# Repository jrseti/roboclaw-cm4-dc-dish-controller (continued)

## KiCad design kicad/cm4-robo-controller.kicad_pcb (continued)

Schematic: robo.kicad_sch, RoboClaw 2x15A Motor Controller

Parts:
A1: ROBOCLAW-2X15A-OEM; MOD-TH_ROBOCLAW-OEM-2X15A; MPN RoboClaw 2x15A OEM; LCSC Part N/A; not fitted
C57, C58, C59, C60, C61, C87, C88: 10nF; CAPC1005X55N; Voltage Rating 50V; Tolerance ±10%; MPN 0402B103K500CT; LCSC Part C301927
C62, C63, C83, C86: 100nF; CAPC1005X55N; Tolerance ±10%; Voltage Rating 16V; MPN CL05B104KO5NNNC; LCSC Part C1525
C80: 1uF; CAPC1608X95N; Tolerance ±10%; Voltage Rating 25V; MPN CL10A105KA8NNNC; LCSC Part C5673
C81, C89: 10uF; CAPC1608X95N; Tolerance ±20%; Voltage Rating 25V; MPN CL10A106MA8NRNC; LCSC Part C96446
D16, D18, D22, D27: TPESD0402G12V; DIOC1005X55N; MPN TPESD0402G12V; LCSC Part C558617
D17, D19, D20: TPESD0402G15V; DIOC1005X55N; MPN TPESD0402G15V; LCSC Part C558618
D21: SMF6.0A; SODFL3718X110N; MPN SMF6.0A; LCSC Part C19077499
D23: SMBJ3V3; DIOM5436X244N; MPN SMBJ3V3-E3/52; LCSC Part C82082
D28: SMAJ20A; DIOM5226X244N; MPN SMAJ20A; LCSC Part C41376408
F3: 100mA; FUSC3216X110N; MPN nSMD010; LCSC Part C70065
F4: 350mA; FUSC3216X110N; MPN 1206L035/60NR; LCSC Part C55109877
F6, F7: 200mA; FUSC1608X100N; MPN SMD0603-020-24V; LCSC Part C19108393
J8, J9: KF2EDGR-2.54-4P; CONN-TH_4P-P2.54_KF2EDGR-2.54-4P; MPN KF2EDGR-2.54-4P; LCSC Part C577596
J10, J12, J13: KF2EDGR-2.54-2P; CONN-TH_P2.54_KF2EDGR-2.54-2P; MPN KF2EDGR-2.54-2P; LCSC Part C577594
J11, J14: KF7620-7.62-2P; CONN-TH_P7.62_KF7620-7.62-2P; MPN KF7620-7.62-2P; LCSC Part C475104
J15: PM254-2-12-Z-8.5; HDR-F-TH_2x12-P2.54-H8.5_PM254_NOPADS; MPN PM254-2-12-Z-8.5; LCSC Part C2897413
J16: PM254-2-09-Z-8.5; HDR-F-TH_2x09-P2.54-H8.5_PM254_NOPADS; MPN PM254-2-09-Z-8.5; LCSC Part C2897410
JP1, JP2, JP4, JP5: Header-Male-2.54_2x3; HDR-TH_6P-P2.54-V-M-R2-C3-S2.54-1; MPN 2.54-2*3PPin; LCSC Part C65114
JP3, JP6: Header-Male-2.54_1x3; HDR-TH_3P-P2.54-V-M-1; MPN 2.54-1*3PPin; LCSC Part C49257
R45, R46, R49, R53, R103, R106: 100Ω; RESC1005X40N; Tolerance ±1%; Voltage Rating 50V; MPN 0402WGF1000TCE; LCSC Part C25076
R47, R51, R100, R102, R104, R105: 1kΩ; RESC1005X40N; Tolerance ±1%; Voltage Rating 50V; MPN 0402WGF1001TCE; LCSC Part C11702
R48, R52, R55: 4.7kΩ; RESC1608X55N; Tolerance ±1%; Voltage Rating 50V; MPN 0603WAF4701T5E; LCSC Part C23162
R50, R54, R56: 47kΩ; RESC1005X40N; Tolerance ±1%; Voltage Rating 50V; MPN 0402WGF4702TCE; LCSC Part C25792
R57, R99: 68kΩ; RESC1005X40N; Tolerance ±1%; Voltage Rating 50V; MPN 0402WGF6802TCE; LCSC Part C36871
R58, R101, R110: 100kΩ; RESC1005X40N; Tolerance ±1%; Voltage Rating 50V; MPN 0402WGF1003TCE; LCSC Part C25741
R107, R108, R109: 20kΩ; RESC1005X40N; Tolerance ±1%; Voltage Rating 50V; MPN 0402WGF2002TCE; LCSC Part C25765
TP32, TP37: TestPoint_Small; TestPoint_Pad_D0.8mm
U16, U19: 74LVC1G17SE-7; SOT65P210X110-5N; MPN 74LVC1G17SE-7; LCSC Part C212314
U18: TPS70933DBVR; SOT95P280X145-5N; MPN TPS70933DBVR; LCSC Part C89347

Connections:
/3V3_CM4: C63.1, C83.1, U16.5 (VCC), U19.5 (VCC); also elsewhere on the board
/CM4/ROBO_RX_MCU: U16.4 (Y); also elsewhere on the board
/CM4/ROBO_TX_MCU: U19.2 (A); also elsewhere on the board
/Robo/AZ_LIMIT: A1.S5, C61.1, R56.2, R108.1
/Robo/AZ_LIMIT_IN: D20.2, J13.1, R55.2, R56.1
/Robo/EL_LIMIT: A1.S4, C60.1, R54.2, R107.1
/Robo/EL_LIMIT_IN: D19.2, J12.1, R52.2, R54.1
/Robo/EN1_A: A1.1A (EN1_A), JP2.4
/Robo/EN1_B: A1.1B (EN1_B), C59.1, R53.2
/Robo/EN2_A: A1.2A (EN2_A), JP5.4
/Robo/EN2_B: A1.2B (EN2_B), C88.1, R106.2
/Robo/ENC1_A_ABS: JP2.5, JP3.2
/Robo/ENC1_A_IN: D16.2 (A), J8.2, JP2.3
/Robo/ENC1_B_IN: D18.2 (A), J8.3, R51.2, R53.1
/Robo/ENC1_V: J8.1, JP1.2, JP1.4, JP1.6
/Robo/ENC2_A_ABS: JP5.5, JP6.2
/Robo/ENC2_A_IN: D22.2 (A), J9.2, JP5.3
/Robo/ENC2_B_IN: D27.2 (A), J9.3, R105.2, R106.1
/Robo/ENC2_V: J9.1, JP4.2, JP4.4, JP4.6
/Robo/ENC_3V3: F3.2, JP1.3, JP4.3
/Robo/ENC_12V: C89.1, D28.1, F4.2, JP1.5, JP4.5, R48.1, R52.1, R55.1
/Robo/ESTOP: A1.S3, C58.1, R50.2, R109.1
/Robo/ESTOP_IN: D17.2, J10.1, R48.2, R50.1
/Robo/M1A: A1.M1A, J11.1
/Robo/M1B: A1.M1B, J11.2
/Robo/M2A: A1.M2A, J14.2
/Robo/M2B: A1.M2B, J14.1
/Robo/RC_5V: A1.5VDC (5VDC_OUT), C80.2, D21.1, F6.1, F7.1, R47.1, R51.1, R102.1, R105.1, R110.2, TP32.1 (1_1), U18.1 (IN)
/Robo/ROBO_S1_RX: R46.1, U19.4 (Y)
/Robo/ROBO_S2_TX: R45.1, U16.2 (A)
/Robo/V_MOTOR: A1.BAT+, F4.1; also elsewhere on the board
GND: C63.2, C83.2, U16.3 (GND), U19.3 (GND); also elsewhere on the board
unnamed: A1.S1 (S1_RX), R46.2
unnamed: A1.S2 (S2_TX), R45.2
unnamed: C57.1, JP2.2, R49.2
unnamed: C62.1, JP5.6, R57.2, R58.1, R104.2
unnamed: C86.1, JP2.6, R99.2, R100.2, R101.1
unnamed: C87.1, JP5.2, R103.2
unnamed: F6.2, JP1.1
unnamed: F7.2, JP4.1
unnamed: JP2.1, R47.2, R49.1
unnamed: JP3.1, R99.1
unnamed: JP3.3, R100.1
unnamed: JP5.1, R102.2, R103.1
unnamed: JP6.1, R57.1
unnamed: JP6.3, R104.1
unnamed: R110.1, TP37.1 (1_1), U18.3 (EN)
unnamed: C81.1, D23.1, F3.1, U18.5 (OUT)
PGND: A1.BAT-, A1.GND, C57.2, C58.2, C59.2, C60.2, C61.2, C62.2, C80.1, C81.2, C86.2, C87.2, C88.2, C89.2, D16.1 (K), D17.1, D18.1 (K), D19.1, D20.1, D21.2, D22.1 (K), D23.2, D27.1 (K), D28.2, J8.4, J9.4, J10.2, J12.2, J13.2, R58.2, R101.2, R107.2, R108.2, R109.2, U18.2 (GND); also elsewhere on the board

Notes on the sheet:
QUAD
F6 / F7: 200 mA PTC (TECHFUSE SMD0603-020-24V, 0.55 ohm) in series with the 5 V option only (JP1 / JP4 1-2). RC_5V is the RoboClaw BEC, which also feeds the RoboClaw logic: a shorted or miswired encoder cable on the 5 V setting would drag it down. F6/F7 trip at 500 mA and reset when the fault clear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
The encoder connectors J8/J9 (field-wired) take their 3.3 V option from U18 (TPS70933, 30 V max, from RC_5V), not 3V3_CM4, so a miswired sensor supply cannot back-feed the CM4 or the GPS. U18 blocks reverse current, so it cannot reach RC_5V either. EN: R110 100k pull-up to RC_5V, TP37 for test (gro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
ABS
3V3
Encoder Inputs
A1 TX buffer (no CM4 back-power)
Sockets for A1 (RoboClaw plugs in)
E-stop / limit switches
ENC_12V sensor supply (JP1 / JP4)
JP5 QUAD: A/B, 1k pull-ups to 5 V, 100R/10nF. JP5 ABS: 0-2 V on A, scale set by JP6
Limit switches, two per motor
RoboClaw
ENC1: A1 EN1 encoder input (motor M1)
JP2 QUAD: A/B, 1k pull-ups to 5 V, 100R/10nF. JP2 ABS: 0-2 V on A, scale set by JP3
ENC2: A1 EN2 encoder input (motor M2)
U16 isolates A1 S2 TX from CM4 GPIO13 (ROBO_RX_MCU); U19 (below the J9 box) isolates CM4 GPIO12 (ROBO_TX_MCU) from A1 S1 RX and its pull-up. A1 runs from the battery while the CM4 can be off (SW1 open, GLOBAL_EN power cycle). Wired direct, A1 would back-power the CM4 through GPIO13 or GPIO12 (abs m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
D23: Vishay SMBJ3V3-E3/52, 600 W SMB TVS. VBR >= 4.1 V, VC 7.3 V @ 50 A, IR <= 200 uA. Holds U18 OUT (7 V abs max) on a J9 miswire until F3 trips. Not a generic SMBJ3.3A: some break down at 6.5 V.
JUMPERS (ENC1: JP1 JP2 JP3, ENC2: JP4 JP5 JP6) JP1/JP4 V+ supply 1-2: 5 V (RC_5V via F6/F7, 200 mA PTC) 3-4: 3.3 V (ENC_3V3, U18) 5-6: 12 V (ENC_12V, battery) Shunt across a row only: 1-3 or 3-5 shorts two rails. JP2/JP5 mode 1-3 + 2-4: QUAD 3-5 + 4-6: ABS JP3/JP6 ABS scale 1-2: 3.3 V sensor -> 2 V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
LIMIT SWITCHES: the RoboClaw has one limit input per motor (S4 = M1, S5 = M2) and supports two switches on it. Wire two NC switches in SERIES per axis (J12 elevation, J13 azimuth): either one opening lets the 4.7k pull-up raise the input. Set Invert (active-high). Both switches share the pin, so th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
U18 EN (pin 3): R110 100k pull-up to RC_5V, TP37 for test. Ground TP37 to hold U18 off, release to run. EN clamps at 6.5 V: keep TP37 under 6 V and never tie EN straight to IN.
EMC: run motor leads in shielded cable, shield clamped 360 deg to the enclosure at the gland (not to J11/J14). Clip-on CM ferrite per pair at entry; 100 nF brush caps at the motors. Keep motor leads away from GNSS/encoder wiring.
J11 = Firgelli motor (elevation): 1 BLUE (+) 2 BROWN (-) Swap to reverse, or invert M1 in Motion Studio.
E-stop and limits: 12 V loops, NC, set Invert. 2 limits/motor: see note.
Motors Output M1 = elevation M2 = azimuth
RC_5V budget: <= 800 mA (BEC). Load: ~20 mA pull-ups + sensors. F6/F7: 200 mA PTC, 5 V option.
Battery voltage (10-14.6 V) for sensors that need it (E6B2-CWZ6C: 5-24 V, 80 mA) and the E-stop / limit-switch loops (4.7k pull-ups). From V_MOTOR, so the return stays on the RoboClaw ground. F4 350 mA PTC, D28 SMAJ20A, C89 10 uF. Encoder pull-ups: RC_5V.
A1 RX buffer (no CM4 back-power)
ROBOCLAW-2X15A-OEM
ENC_3V3: 3.3 V sensor supply (U18) for JP1 / JP4
J8 = ENC1 (M1) J9 = ENC2 (M2) 1 V+ (JP1/JP4) 2 A or analog 3 B (quad only) 4 GND

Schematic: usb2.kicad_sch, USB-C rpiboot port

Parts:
C85: 100nF; CAPC1005X55N; Tolerance ±10%; Voltage Rating 16V; MPN CL05B104KO5NNNC; LCSC Part C1525
D24: SMF6.0A; SODFL3718X110N; MPN SMF6.0A; LCSC Part C19077499
F5: 50mA; FUSC1608X100N; MPN SMD0603-005-24V; LCSC Part C70046
R59, R61: 2.2kΩ; RESC1005X40N; Tolerance ±1%; Voltage Rating 50V; MPN 0402WGF2201TCE; LCSC Part C25879
R60: 10kΩ; RESC1005X40N; Tolerance ±1%; Voltage Rating 50V; MPN 0402WGF1002TCE; LCSC Part C25744
R62, R63: 5.1kΩ; RESC1005X40N; Tolerance ±1%; Voltage Rating 50V; MPN 0402WGF5101TCE; LCSC Part C25905
TP28, TP33: TestPoint_Small; TestPoint_Pad_D0.8mm
U17: 74LVC1G07SE-7; SOT65P210X110-5N; MPN 74LVC1G07SE-7; LCSC Part C67531
USBC1: TYPE-C-31-M-12; USB-C_SMD-TYPE-C-31-M-12_1; MPN TYPE-C-31-M-12; LCSC Part C165948

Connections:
/3V3_CM4: C85.1, R60.1, U17.5 (VCC); also elsewhere on the board
/CM4/USB_OTG_ID: R60.2, U17.4 (Y); also elsewhere on the board
/CM4/usb/HSD2+: USBC1.A6 (DP1), USBC1.B6 (DP2); also elsewhere on the board
/CM4/usb/HSD2-: USBC1.A7 (DN1), USBC1.B7 (DN2); also elsewhere on the board
/CM4/usb/usb2/VBUS_DET: R59.1, R61.2, U17.2 (A)
/CM4/usb/usb2/VBUS_USBC: F5.1, TP33.1 (1_1), USBC1.A4B9 (VBUS), USBC1.B4A9 (VBUS)
CHASSIS: USBC1.1 (EH), USBC1.2 (EH), USBC1.3 (EH), USBC1.4 (EH); also elsewhere on the board
GND: C85.2, D24.2, R61.1, R62.2, R63.2, U17.3 (GND), USBC1.A1B12 (GND), USBC1.B1A12 (GND); also elsewhere on the board
unnamed: D24.1, F5.2, R59.2, TP28.1 (1_1)
unnamed: R62.1, USBC1.A5 (CC1)
unnamed: R63.1, USBC1.B5 (CC2)

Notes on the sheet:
USB-C Port for CM4 Flashing (rpiboot)
U17 is open-drain, powered from 3V3_CM4. With the CM4 off, Y is high-Z and R60 is unpowered, so U2 Sel and CM4 USB_OTG_ID are never driven (CM4 datasheet 5.1). 74LVC Ioff: A tolerates VBUS_DET at VCC = 0.
USB_OTG_ID: high = CM4 device mode (rpiboot), low/GND = CM4 host. Needs otg_mode=1 in config.txt. USBC1 VBUS: 5.0 V nom (4.75 V min / 5.5 V max). No USB-PD controller; CC has 5.1 kΩ Rd only. VBUS detect: R59/R61 (2.75 V max) -> U17 open-drain -> USB_OTG_ID. VBUS current: 1.25 mA continuous / 1.25 m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
F5 (TECHFUSE SMD0603-005-24V, 50 mA hold, 200 mA trip, 2-4 ohm) sits between USBC1 VBUS and the D24 / R59 / TP28 node. A short on that node (D24 failed, TP28 probe slip) trips F5 instead of relying on the USB source current limit. At 1.25 mA F5 drops < 10 mV, so VBUS detect is unaffected; its 24 V 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
VBUS detect buffer

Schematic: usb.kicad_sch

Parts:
C3, C4: 15pF; CAPC1005X55N; Tolerance ±5%; Voltage Rating 50V; MPN 0402CG150J500NT; LCSC Part C1548
C5, C9, C10, C11, C12, C13: 10uF; CAPC2012X145N; Tolerance ±10%; Voltage Rating 10V; MPN CL21B106KPQNNNE; LCSC Part C32635
C6, C8, C15, C16, C17, C18, C19, C20, C21: 100nF; CAPC1005X55N; Tolerance ±10%; Voltage Rating 16V; MPN CL05B104KO5NNNC; LCSC Part C1525
C7: 100uF; CAPMP7343X310N; Tolerance ±20%; Voltage Rating 10V; MPN SA11AM101A19R15XXX; LCSC Part C135491
C14: 10uF; CAPC2012X145N; VOLTAGE RATING 10V; Tolerance ±10%; MPN CL21B106KPQNNNE; LCSC Part C32635
D6: BAT54C; SOT95P280X110-3N; MPN BAT54C,215; LCSC Part C37704
D8: SMF6.0A; SODFL3718X110N; MPN SMF6.0A; LCSC Part C19077499
R10: 12kΩ; RESC1005X40N; Tolerance ±1%; Voltage Rating 50V; MPN 0402WGF1202TCE; LCSC Part C25752
R11: 100kΩ; RESC1608X55N; Tolerance ±1%; Voltage Rating 75V; MPN 0603WAF1003T5E; LCSC Part C25803
R12, R13, R14, R15: 36kΩ; RESC1005X40N; Tolerance ±1%; Voltage Rating 50V; MPN FRC0402F3602TS; LCSC Part C2930004
R16, R64, R94, R95, R96, R97: 10kΩ; RESC1005X40N; Tolerance ±1%; Voltage Rating 50V; MPN 0402WGF1002TCE; LCSC Part C25744
R17: 15kΩ; RESC1005X40N; Tolerance ±1%; Voltage Rating 50V; MPN 0402WGF1502TCE; LCSC Part C25756
TP8, TP9, TP10, TP29, TP34, TP35: TestPoint_Small; TestPoint_Pad_D0.8mm
U2: FSUSB42MUX; SOP50P500X110-10N; MPN FSUSB42MUX; LCSC Part C11355
U3: USB2514B-I/M2; QFN50P600X600X100-37N; MPN USB2514B-I/M2; LCSC Part C220679
U4: AP22653W6-7; SOT95P280X145-6N; MPN AP22653W6-7; LCSC Part C2158037
U5, U6: TPD4EUSB30DQAR; SON50P100X250X60-10N; MPN TPD4EUSB30DQAR; LCSC Part C90627
USB1: Double layer DIP 90° black; USB-A-TH_USB-M-51; MPN 907-111A1022D10200; LCSC Part C12049
X1: 24MHz; CRYSTAL-SMD_4P-L3.2-W2.5-BL; Frequency Tolerance ±10ppm; MPN X322524MOB4SI; LCSC Part C70590

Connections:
/3V3_CM4: C13.2, C14.2, C15.1, C16.1, C17.1, C18.1, C19.1, C20.1, C21.1, R16.2, R94.1, R95.1, R96.1, R97.1, U2.1 (VCC), U3.5 (VDDA33), U3.10 (VDDA33), U3.15 (VDD33), U3.23 (VDD33), U3.27 (VBUS_DET), U3.29 (VDDA33), U3.36 (VDDA33); also elsewhere on the board
/5V: C5.2, C6.1, U4.1 (IN); also elsewhere on the board
/CM4/USB2_N: U2.3 (D+); also elsewhere on the board
/CM4/USB2_P: U2.4 (D-); also elsewhere on the board
/CM4/USB_OTG_ID: U2.2 (Sel); also elsewhere on the board
/CM4/nEXTRST: TP35.1 (1_1), U3.26 (RESET_N); also elsewhere on the board
/CM4/usb/HD1_N: U3.1 (USBDM_DN1/PRT_DIS_M1), U6.5 (D2-), U6.6 (D2-), USB1.2 (D-)
/CM4/usb/HD1_P: U3.2 (USBDP_DN1/PRT_DIS_P1), U6.4 (D2+), U6.7 (D2+), USB1.3 (D+)
/CM4/usb/HD2_N: U3.3 (USBDM_DN2/PRT_DIS_M2), U6.2 (D1-), U6.9 (D1-), USB1.6 (D-)
/CM4/usb/HD2_P: U3.4 (USBDP_DN2/PRT_DIS_P2), U6.1 (D1+), U6.10 (D1+), USB1.7 (D+)
/CM4/usb/HD3_N: R94.2, U3.6 (USBDM_DN3/PRT_DIS_M3)
/CM4/usb/HD3_P: R95.2, U3.7 (USBDP_DN3/PRT_DIS_P3)
/CM4/usb/HD4_N: R96.2, U3.8 (USBDM_DN4/PRT_DIS_M4)
/CM4/usb/HD4_P: R97.2, U3.9 (USBDP_DN4/PRT_DIS_P4)
/CM4/usb/HSD2+: U2.8 (HSD2-), U5.4 (D2+), U5.7 (D2+); also elsewhere on the board
/CM4/usb/HSD2-: U2.9 (HSD2+), U5.5 (D2-), U5.6 (D2-); also elsewhere on the board
/CM4/usb/MUX_OE: R64.1, TP29.1 (1_1), U2.10 (~OE)
/CM4/usb/Net-(U5-ILIM): R17.1, TP9.1 (1_1), U4.5 (ILIM)
/CM4/usb/PWR1: D6.1 (A), U3.12 (PRTPWR1/BC_EN1)
/CM4/usb/PWR2: D6.2 (A), U3.16 (PRTPWR2/BC_EN2)
/CM4/usb/U5_EN: D6.3 (K), R11.1, TP34.1 (1_1), U4.3 (EN/~EN)
/CM4/usb/USB_HUB_N: U2.7 (HSD1+), U3.30 (USBDM_UP)
/CM4/usb/USB_HUB_P: U2.6 (HSD1-), U3.31 (USBDP_UP)
/CM4/usb/VBUS: C7.1, C8.1, C9.2, C10.2, C11.2, C12.2, D8.1, U4.6 (OUT), USB1.1 (VCC), USB1.5 (VCC)
/CM4/usb/nOCS1: R16.1, U3.13 (OCS_N1), U3.17 (OCS_N2), U3.19 (OCS_N3), U3.21 (OCS_N4), U4.4 (~FAULT)
CHASSIS: USB1.9; also elsewhere on the board
GND: C3.2, C4.2, C5.1, C6.2, C7.2, C8.2, C9.1, C10.1, C11.1, C12.1, C13.1, C14.1, C15.2, C16.2, C17.2, C18.2, C19.2, C20.2, C21.2, D8.2, R10.1, R11.2, R12.1, R13.1, R14.1, R15.1, R17.2, R64.2, TP8.1 (1_1), TP10.1 (1_1), U2.5 (GND), U3.37 (EP), U4.2 (GND), U5.3 (GND), U5.8 (GND), U6.3 (GND), U6.8 (GND), USB1.4 (GND), USB1.8 (GND), X1.2 (GND), X1.4 (GND); also elsewhere on the board
unnamed: R15.2, U3.25 (HS_IND/CFG_SEL1)
unnamed: R10.2, U3.35 (RBIAS)
unnamed: R12.2, U3.24 (SCL/SMBCLK/CFG_SEL0)
unnamed: R13.2, U3.22 (SDA/SMBBATA/NON_REM1)
unnamed: R14.2, U3.28 (SUSP_IND/LOCAL_PWR/NON_REM0)
unnamed: C4.1, U3.33 (XTALIN/CLKIN), X1.1 (OSC1)
unnamed: C3.1, U3.32 (XTALOUT), X1.3 (OSC2)

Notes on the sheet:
3.3V Caps for U2 and U3 VDD/VCC.
USB-A ESD
Place each 100nF next to its own U3 supply pin (pins 5, 10, 15, 23, 29, 36) One 100nF place near pin 1 of U2
Current-limited high-side switch
Supplies and protects the 5V going out to both USB-A ports ILIM with 15K resistor limits to ~1.75A shared across USB1
Reset: RESET_N (pin 26) is on nEXTRST, which leaves this sheet.
Hub ports 3 and 4 are not used. 10k pull-ups on D+ and D- disable them: the PRT_DIS straps are sampled at RESET_N (USB2514B, CFG_SEL=00).
24MHz
USB-C ESD
U4 port power, diode-OR (D6, R11). The hub straps CFG_SEL=00: individual port power switching and OC sensing (USB2514B Table 5-1). U4 feeds both USB1 ports, so its EN is the OR of PRTPWR1-2: VBUS stays on while either port is enabled and drops only when both are off. Ports 3 and 4 are disabled by s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
USB - 2 Ports
C7 SUBSTITUTION (2026-11-01) Preferred part: Panasonic EEFCX0J101R (LCSC C189619), 100uF 6.3V polymer, 15mOhm, 5.1A ripple. Out of stock at JLCPCB since 2026-10-30 (min order 14), so AISHI SA11AM101A19R15XXX (C135491) is fitted: same 7.3x4.3mm D-case footprint, 100uF 10V, 15mOhm, 2.5A ripple, which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
Stacked USB connectors
Place ESD protection next to respective USB ports
Unused hub ports 3 and 4
4-Port USB Hub (all 4 ports used)
Protects both USB-A ports (4 lines). Diode clamps VBUS. Place both at USB1.

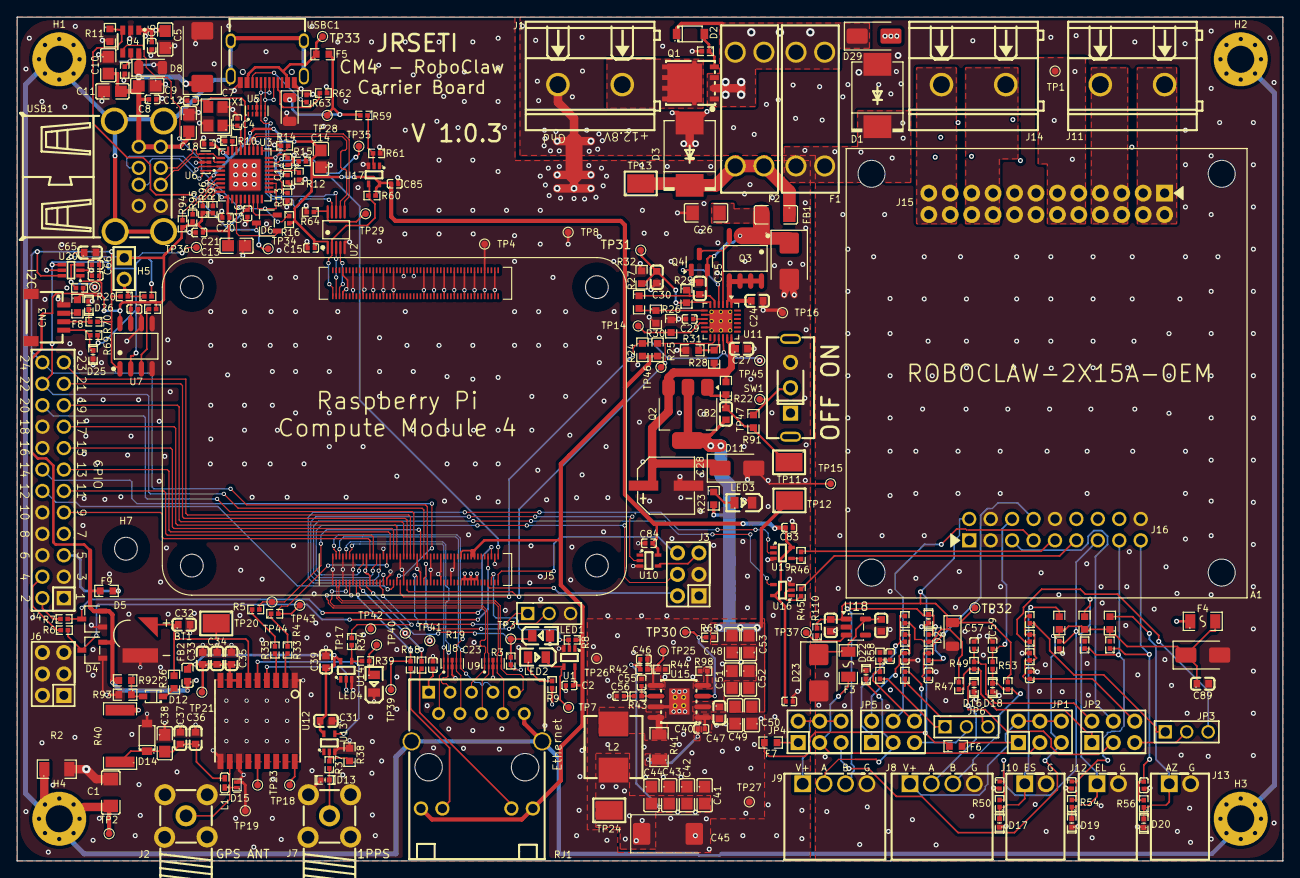
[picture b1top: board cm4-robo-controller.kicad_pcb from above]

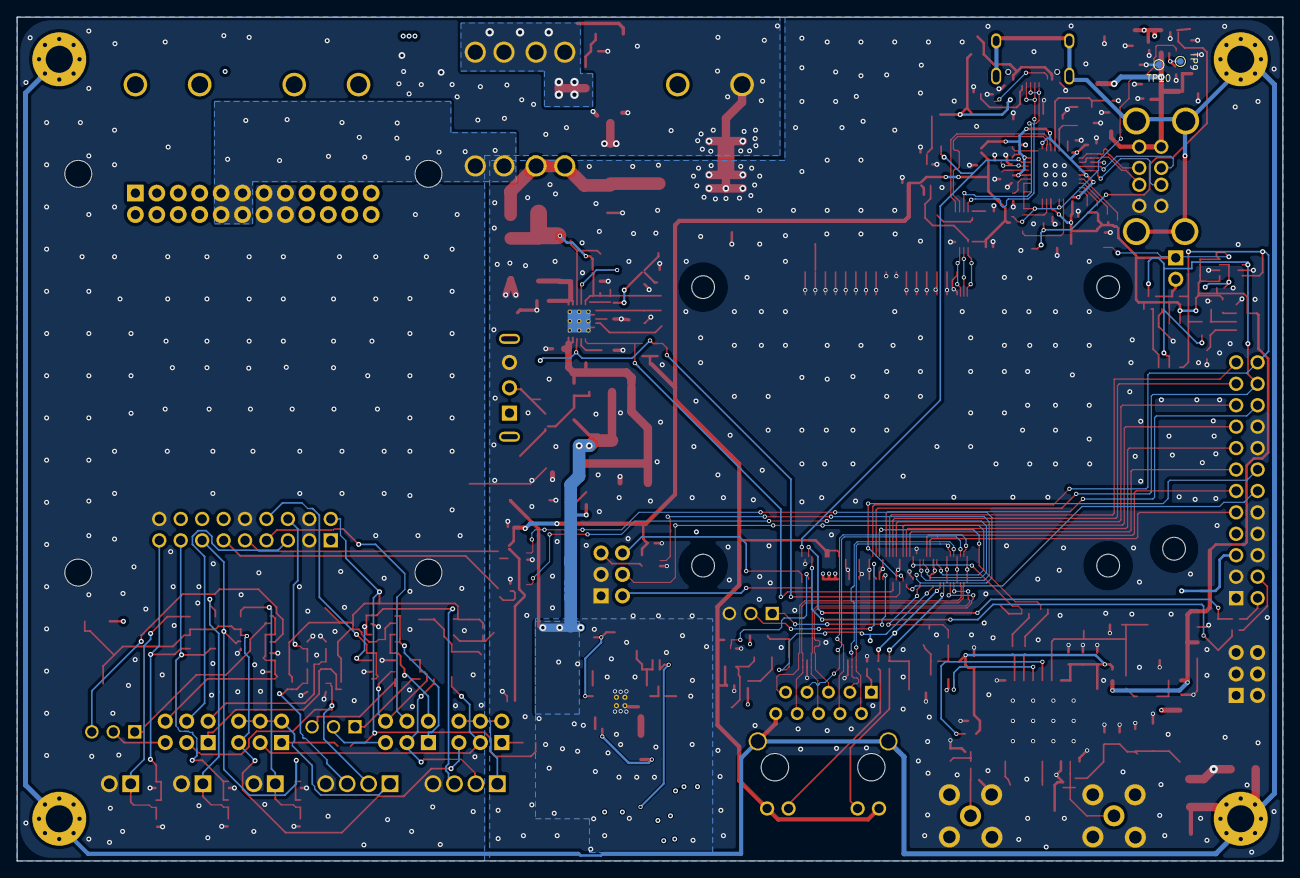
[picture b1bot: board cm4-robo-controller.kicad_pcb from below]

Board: 4 copper layers, 150.0 x 100.0 mm, 316 parts (2 on the bottom side), 184 nets.

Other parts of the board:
C1: 4.7nF; CAPC3216X180N
H1, H2, H3, H4: M3; MountingHole_3.2mm_M3_Pad_Via
H7: M2.5; MountingHole_2.7mm_M2.5
NT1: NetTie; NetTie-2_SMD_Pad2.0mm
R2: 1MΩ; RESC3216X70N
TP1, TP2: TestPoint_Small; TestPoint_Pad_D0.8mm

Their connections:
/Robo/V_MOTOR: TP1.1 (1_1); also elsewhere on the board
CHASSIS: C1.1, H1.1 (1_1), H2.1 (1_1), H3.1 (1_1), H4.1 (1_1), R2.1, TP2.1 (1_1); also elsewhere on the board
GND: C1.2, NT1.2, R2.2; also elsewhere on the board
PGND: NT1.1; also elsewhere on the board

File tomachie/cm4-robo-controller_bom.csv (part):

BILL OF MATERIAL
PCA P/N,cm4-robo-controller,DESCRIPTION,,DATE,

Qty,Part Number,Footprint,Description,Value,Units,Tolerance,Locations
1,ROBOCLAW-2X15A-OEM,MOD-TH_ROBOCLAW-OEM-2X15A,"OEM RoboClaw 2x15A dual channel brushed DC motor controller module, 6-34V, 15A/ch (30A peak), packet-serial / RC / analog control",0,,,A1
1,CM4004008,Raspberry-Pi-4-Compute-Module,,0,,,A2
1,ML414H-IV01E,ML414H-IV01E,"Seiko ML414H-IV01E 3V 1.0mAh rechargeable lithium coin cell, 4.8x1.4mm, reflowable (260C peak). Charge 2.8-3.1V via series resistor.",0,,,BT1
1,1206B472K202NT,CAPC3216X180N,2kV 4.7nF X7R ±10% 1206 Multilayer Ceramic Capacitors MLCC - SMD/SMT ROHS,4.7,nF,±10%,C1
21,CL05B104KO5NNNC,CAPC1005X55N,100nF 16V X7R ±10% 0402 Multilayer Ceramic Capacitors MLCC - SMD/SMT ROHS,100,nF,±10%,"C2, C6, C8, C15, C16, C17, C18, C19, C20, C21, C23, C29, C40, C62, C63, C64, C66, C83, C84, C85, C86"
2,0402CG150J500NT,CAPC1005X55N,15pF 50V C0G ±5% 0402 Multilayer Ceramic Capacitors MLCC - SMD/SMT ROHS,15,pF,±5%,"C3, C4"
1,SM04B-SRSS-TB(LF)(SN),JST_SH_SM04B-SRSS-TB_1x04-1MP_P1.00mm_Horizontal,,0,,,CN3
12,CL21B106KPQNNNE,CAPC2012X145N,10V 10uF X7R ±10% 0805 Multilayer Ceramic Capacitors MLCC - SMD/SMT ROHS,10,uF,±10%,"C5, C9, C10, C11, C12, C13, C14, C38, C41, C42, C43, C44"
2,SA11AM101A19R15XXX,CAPMP7343X310N,"-55℃~+105℃ 100uF 15mΩ@100kHz 2000hrs@105℃ 2.5A@100kHz 10V Polarized Polymer ±20% SMD,7.3x4.3mm Polymer Aluminum Capacitors ROHS",100,uF,±20%,"C7, C45"
1,CL05A475MP5NRNC,CAPC1005X55N,10V 4.7uF X5R ±20% 0402 Multilayer Ceramic Capacitors MLCC - SMD/SMT ROHS,4.7,uF,±20%,C22
8,CC0603KRX7R9BB104,CAPC1608X95N,100nF 50V X7R ±10% 0603 Multilayer Ceramic Capacitors MLCC - SMD/SMT ROHS,100,nF,±10%,"C24, C25, C27, C31, C34, C35, C39, C47"
1,TCC1206X7R106K500HT,CAPC3216X180N,10uF 50V X7R ±10% 1206 Multilayer Ceramic Capacitors MLCC - SMD/SMT ROHS,10,uF,±10%,C26
1,JVJ35V220M6x8,CAPAE660X770N,"-55℃~+105℃ 190mA@120Hz 2000hrs@105℃ 220uF 35V 6.3mm 7.7mm ±20% SMD,D6.3xL7.7mm Aluminum Electrolytic Capacitors - SMD ROHS",220,uF,±20%,C28
2,CL10A105KA8NNNC,CAPC1608X95N,1uF 25V X5R ±10% 0603 Multilayer Ceramic Capacitors MLCC - SMD/SMT ROHS,1,uF,±10%,"C30, C80"
1,CL10A105KB8NNNC,CAPC1608X95N,1uF 50V X5R ±10% 0603 Multilayer Ceramic Capacitors MLCC - SMD/SMT ROHS,1,uF,±10%,C32
3,CL10A106MA8NRNC,CAPC1608X95N,10uF 25V X5R ±20% 0603 Multilayer Ceramic Capacitors MLCC - SMD/SMT ROHS,10,uF,±20%,"C33, C81, C89"
1,CL10C470JB8NNNC,CAPC1608X95N,47pF 50V C0G ±5% 0603 Multilayer Ceramic Capacitors MLCC - SMD/SMT ROHS,47,pF,±5%,C36
1,0603B103K500NT,CAPC1608X95N,10nF 50V X7R ±10% 0603 Multilayer Ceramic Capacitors MLCC - SMD/SMT ROHS,10,nF,±10%,C37
6,GRM21BC8YA106KE11L,CAPC2012X145N,10uF 35V X6S ±10% 0805 Multilayer Ceramic Capacitors MLCC - SMD/SMT ROHS,10,uF,±10%,"C48, C49, C50, C51, C52, C53"
1,CC0402KRX7R9BB122,CAPC1005X55N,1.2nF 50V X7R ±10% 0402 Multilayer Ceramic Capacitors MLCC - SMD/SMT ROHS,1.2,nF,±10%,C56
7,0402B103K500CT,CAPC1005X55N,10nF 50V X7R ±10% 0402 Multilayer Ceramic Capacitors MLCC - SMD/SMT ROHS,10,nF,±10%,"C57, C58, C59, C60, C61, C87, C88"
1,CL10A106KP8NNNC,CAPC1608X95N,10V 10uF X5R ±10% 0603 Multilayer Ceramic Capacitors MLCC - SMD/SMT ROHS,10,uF,±10%,C65
1,CL10B473KB8NNNC,CAPC1608X95N,47nF 50V X7R ±10% 0603 Multilayer Ceramic Capacitors MLCC - SMD/SMT ROHS,47,nF,±10%,C82
2,SMCJ18A,DIOM7959X262N,-55℃~+150℃ 1.5kW@10/1000us 18V 22.1V 29.2V 51.4A@10/1000us 5uA TVS Unidirectional SMC ESD and Surge Protection (TVS/ESD) ROHS,0,,,"D1, D3"
1,BZT52C15,SOD3716X135N,-55℃~+150℃ 350mW 14.25V~15.75V 15V 30Ω SOD-123 Zener Diodes ROHS,0,,,D2
2,"BAT54S,215",SOT95P280X110-3N,1 Pair Series Connection 200mA 30V 800mV@100mA SOT-23 Schottky Diodes ROHS,0,,,"D4, D5"
1,"BAT54C,215",SOT95P280X110-3N,1 Pair Common Cathode 200mA 30V 800mV@100mA SOT-23 Schottky Diodes ROHS,0,,,D6
3,SMF6.0A,SODFL3718X110N,-55℃~+150℃ 1 10.3V 19.4A@10/1000us 200W@10/1000us 400uA 6V 7.37V IEC 61000-4-2 TVS Unidirectional SOD-123FL ESD and Surge Protection (TVS/ESD) ROHS,0,,,"D8, D21, D24"
1,SMBJ18CA,DIOM5436X244N,-55℃~+150℃ 1 18V 20.55A 22.1V 29.2V 5uA 600W@10/1000us Bidirectional IEC 61000-4-2 TVS DO-214AA(SMB) ESD and Surge Protection (TVS/ESD) ROHS,0,,,D10
2,SMAJ20A,DIOM5226X244N,-55℃~+150℃ 1 12.3A@10/1000us 1uA 20V 24.5V 32.4V 400W IEC 61000-4-2 TVS Unidirectional DO-214AC(SMA) ESD and Surge Protection (TVS/ESD) ROHS,0,,,"D11, D28"
1,1N4148WS,SOD2513X110N,1N4148WS T4,0,,,D12
5,TPESD0402G12V,DIOC1005X55N,12VWM 40VC 0402,0,,,"D13, D16, D18, D22, D27"
1,BZT52C4V7,SOD3716X135N,-55℃~+150℃ 350mW 4.47V~4.94V 4.7V 80Ω SOD-123 Zener Diodes ROHS,0,,,D14
1,SESD0402X1UN-0020-090,DIOC1006X40N,"0.25pF 7V working 9.2V clamp 2A@8/20us unidirectional TVS, IEC 61000-4-2, DFN1006-2. Pin 1 = cathode.",0,,,D15
3,TPESD0402G15V,DIOC1005X55N,15VWM 40VC 0402,0,,,"D17, D19, D20"
1,SMBJ3V3-E3/52,DIOM5436X244N,-55℃~+175℃ 1 600W@10/1000us 50A@10/1000us 200uA 3.3V 4.1V 7.3V TVS Unidirectional SMB(DO-214AA) ESD and Surge Protection (TVS/ESD) ROHS,0,,,D23
2,TPESD0402G05V,DIOC1005X55N,5VWM 40VC 0402,0,,,"D25, D26"
1,SS54,DIOM5226X244N,"Schottky diode 5A 40V SMA (DO-214AC), Vf 0.55V at 5A",0,,,D29
1,BLM31KN121SN1L,INDC3216X130N,-55℃~+125℃ 1 120Ω@100MHz 6A 9mΩ ±25% 1206 Ferrite Beads ROHS,0,,±25%,FB1
1,3557-2,FUSE-TH_4P-L19.8-W6.7_3557-2,"PCB fuse holder for ATO/ATC blade fuse, 30A, THT (fuse fitted separately)",0,,,F1
1,BLM18KG121TN1D,INDC1608X95N,1 120Ω@100MHz 30mΩ 3A ±25% 0603 Ferrite Beads ROHS,0,,±25%,FB2
1,3557-2,FUSE-TH_4P-L19.8-W6.7_3557-2,"PCB fuse holder for ATO/ATC blade fuse, 30A, THT (fuse fitted separately)",0,,,F2
1,nSMD010,FUSC3216X110N,"PTC resettable fuse 100mA hold 250mA trip 60V 1206, 1.6 ohm initial",0,,,F3
1,1206L035/60NR,FUSC3216X110N,"PTC resettable fuse 350mA hold 750mA trip 60V 1206, 0.25 ohm initial, 1.5 ohm max after trip",0,,,F4
1,SMD0603-005-24V,FUSC1608X100N,"PTC resettable fuse 50mA hold 200mA trip 24V 0603, 2 ohm initial, 25 ohm max after trip",0,,,F5
2,SMD0603-020-24V,FUSC1608X100N,"PTC resettable fuse 200mA hold 500mA trip 24V 0603, 0.55 ohm initial, 3.5 ohm max after trip",0,,,"F6, F7"
2,SMD0603-010-24V,FUSC1608X100N,"PTC resettable fuse 100mA hold 300mA trip 24V 0603, 0.9 ohm initial, 10 ohm max after trip",0,,,"F8, F9"
1,B-2100S02P-A110,HDR-TH_2P-P2.54-V-M-1,,0,,,H5
3,KF7620-7.62-2P,CONN-TH_P7.62_KF7620-7.62-2P,"-40℃~+105℃ 1 10~22 1x2P 2 2P 32A 4 450V 7.62mm Green Through Hole Plugin,P=7.62mm Screw Terminal Blocks ROHS",0,,,"J1, J11, J14"
2,SMA-KWE_C7498154,SMA-TH_SMA-KWE_C7498154,-45℃~+80℃ 1 14.6mm 335V 4.65mm 50Ω 6GHz Bent tip Board Side Inner hole Plugin Coaxial Connectors (RF) ROHS,0,,,"J2, J7"
6,2.54-2*3PPin,HDR-TH_6P-P2.54-V-M-R2-C3-S2.54-1,2.54mm 2*3P,0,,,"J3, J6, JP1, JP2, JP4, JP5"
1,2541WV-2x12P,HDR-TH_24P-P2.54-V-M-R2-C12-S2.54,"-55℃~+105℃ 2 2.54mm 2.54mm 2.54mm 24P 2x12P 3A 3mm 6mm Brass Gold Pin Header Through Hole Plugin,P=2.54mm Pin Headers ROHS",0,,,J4
3,2.54-1*3PPin,HDR-TH_3P-P2.54-V-M-1,2.54mm 1*3P,0,,,"J5, JP3, JP6"
2,KF2EDGR-2.54-4P,CONN-TH_4P-P2.54_KF2EDGR-2.54-4P,,0,,,"J8, J9"
3,KF2EDGR-2.54-2P,CONN-TH_P2.54_KF2EDGR-2.54-2P,,0,,,"J10, J12, J13"
1,PM254-2-12-Z-8.5,HDR-F-TH_2x12-P2.54-H8.5_PM254_NOPADS,"2.54mm 2x12P female header socket, 8.5mm, 3A/contact, through hole. Socket for the RoboClaw OEM module; no electrical pins - the socket tails solder into the A1 footprint holes.",0,,,J15
1,PM254-2-09-Z-8.5,HDR-F-TH_2x09-P2.54-H8.5_PM254_NOPADS,"2.54mm 2x09P female header socket, 8.5mm, 3A/contact, through hole. Socket for the RoboClaw OEM module; no electrical pins - the socket tails solder into the A1 footprint holes.",0,,,J16
2,DF40C-100DS-0.4V(51),DF40C-100DS-0.4V_BOM-ONLY,"Hirose DF40C 100-pin 0.4 mm receptacle, 1.5 mm stack height. CM4 mezzanine connector; BOM and placement only, pads are in the CM4 footprint.",0,,,"J17, J18"
1,LQG15HS27NJ02D,INDC1005X55N,1.7GHz 27nH 350mA 460mΩ 8@100MHz ±5% 0402 Inductors (SMD) ROHS,27,nH,±5%,L1
2,KT-0805G,LEDC2012X110N,0805,0,,,"LED1, LED3"
1,KT-0805R,LEDC2012X110N,0805,0,,,LED2
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
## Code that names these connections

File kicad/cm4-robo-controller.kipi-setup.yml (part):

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- /CM4/EP3-
- /CM4/ETH_LEDG
- /CM4/GLOBAL_EN
- /CM4/GPIO0
- /CM4/GPIO17
- /CM4/GPIO19
- /CM4/GPIO22
- /CM4/GPIO26
- /CM4/GPIO27
- /CM4/GPS_RX_MCU
- /CM4/GPS_TX_MCU
- /CM4/I2C/OS
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- /Robo/ROBO_S2_TX
- Net-(A1-S1_RX)
- Net-(A1-S2_TX)
- Net-(A2A-GPIO4)
- Net-(A2A-GPIO5)
- Net-(A2A-PI_nLED_Activity)
- Net-(C23-Pad1)
- Net-(C24-Pad1)
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
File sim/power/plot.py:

"""Plot the power-sheet simulation results (run.sh first). Needs matplotlib."""
import os
import numpy as np
import matplotlib
matplotlib.use("Agg")
import matplotlib.pyplot as plt

R = os.path.join(os.path.dirname(os.path.abspath(__file__)), "results")


def load(name):
    with open(os.path.join(R, name)) as f:
        cols = f.readline().split()
    d = np.loadtxt(os.path.join(R, name), skiprows=1)
    return {c.lower(): d[:, i] for i, c in enumerate(cols)}


def thr(ax, y, text, c="r"):
    ax.axhline(y, ls=":", c=c, lw=1)
    ax.annotate(text, (1, y), xycoords=("axes fraction", "data"), ha="right", va="bottom",
                fontsize=8, color=c)


def finish(ax, title, ylabel, xlabel="ms"):
    ax.set_title(title)
    ax.set_ylabel(ylabel)
    ax.set_xlabel(xlabel)
    ax.grid(alpha=.3)
    ax.legend(fontsize=8, loc="best")


# Start-up
d = load("startup.dat")
t = d["time"] * 1e3
fig, ax = plt.subplots(2, 2, figsize=(11, 7))
ax[0, 0].plot(t, d["v(vbatf)"], label="V_BAT_F")
ax[0, 0].plot(t, d["v(efo)"], label="EFUSE_OUT")
ax[0, 0].plot(t, d["v(v12)"], "--", label="12V rail")
ax[0, 0].plot(t, d["v(vo5)"], label="5V (buck output)")
thr(ax[0, 0], 11.41, "PGOOD rises 11.41 V")
finish(ax[0, 0], "Rails", "V")
ax[0, 1].plot(t, d["v(uvlo)"], label="UVLO pin (C30 filtered)")
ax[0, 1].plot(t, d["v(dvdt)"], label="dVdT pin")
thr(ax[0, 1], 1.21, "UVLO 1.21 V")
finish(ax[0, 1], "U11 control pins", "V")
ax[1, 0].plot(t, d["i(vsef)"], label="U11 current")
thr(ax[1, 0], 3.08, "IOL 3.08 A")
finish(ax[1, 0], "eFuse current", "A")
ax[1, 1].plot(t, d["v(pg)"], label="PGOOD_12V (3.3 V logic)")
ax[1, 1].plot(t, d["v(bgate,vbatf)"], label="Q3 gate-source (BGATE)")
finish(ax[1, 1], "PGOOD and blocking FET", "V")
fig.suptitle("Start-up: 12.8 V battery plugged in at 1 ms, SW1 on, 3 A on 5V")
fig.tight_layout()
fig.savefig(os.path.join(R, "startup.png"), dpi=110)

# SW1 switched on
fig, ax = plt.subplots(2, 2, figsize=(11, 7))
for q, lab in (("0", "earlier design"), ("1", "as built (R91, C82)")):
    d = load(f"sw1_soft{q}.dat")
    t = d["time"] * 1e3
    m = (t > 149.95) & (t < 150.3)
    ax[0, 0].plot((t[m] - 150) * 1e3, d["v(efo)"][m], label=f"EFUSE_OUT, {lab}")
    ax[0, 1].plot((t[m] - 150) * 1e3, d["i(vsq2)"][m], label=f"Q2 current, {lab}")
    ax[0, 1].plot((t[m] - 150) * 1e3, d["i(vsef)"][m], "--", label=f"U11 current, {lab}")
    m2 = (t > 149) & (t < 180)
    ax[1, 0].plot(t[m2] - 150, d["v(v12)"][m2], label=f"12V rail, {lab}")
    ax[1, 0].plot(t[m2] - 150, d["v(vo5)"][m2], "--", label=f"5V, {lab}")
    ax[1, 1].plot((t[m] - 150) * 1e3, d["v(pg)"][m], label=f"PGOOD, {lab}")
thr(ax[0, 0], 10.58, "PGOOD falls 10.58 V")
thr(ax[0, 1], 4.62, "1.5 x IOL fast trip 4.6 A")
finish(ax[0, 0], "EFUSE_OUT when SW1 closes", "V", "µs after SW1")
finish(ax[0, 1], "Inrush current", "A", "µs after SW1")
finish(ax[1, 0], "12V rail and 5V", "V", "ms after SW1")
finish(ax[1, 1], "PGOOD_12V", "V", "µs after SW1")
fig.suptitle("SW1 switched on with U11 already up (battery 12.8 V)")
fig.tight_layout()
fig.savefig(os.path.join(R, "sw1.png"), dpi=110)

# Brownout
fig, ax = plt.subplots(1, 2, figsize=(11, 4))
for v in ("12.8", "12.0", "11.4"):
    d = load(f"brownout_{v}.dat")
    t = d["time"] * 1e3
    m = t > 100
    ax[0].plot(t[m], d["v(efo)"][m], label=f"battery {v} V")
    ax[1].plot(t[m], d["v(pg)"][m], label=f"battery {v} V")
thr(ax[0], 11.41, "PGOOD rises 11.41 V")
thr(ax[0], 10.58, "PGOOD falls 10.58 V")
ax[0].axvspan(150, 450, color="k", alpha=.06)
ax[1].axvspan(150, 450, color="k", alpha=.06)
finish(ax[0], "EFUSE_OUT (15 A motor surge 150-450 ms)", "V")
finish(ax[1], "PGOOD_12V", "V")
fig.tight_layout()
fig.savefig(os.path.join(R, "brownout.png"), dpi=110)

# OVP
d = load("ovp_soft1.dat")
t = d["time"] * 1e3
fig, ax = plt.subplots(1, 3, figsize=(14, 4))
m = (t > 140) & (t < 300)
for k, lab in (("v(vbatf)", "V_BAT_F"), ("v(efo)", "EFUSE_OUT"), ("v(v12)", "12V rail"), ("v(vo5)", "5V")):
    ax[0].plot(t[m], d[k][m], label=lab)
thr(ax[0], 17.96, "OVP 17.96 V")
thr(ax[0], 4.75, "CM4 min 4.75 V")
finish(ax[0], "Battery rail at 21.5 V from 150 to 250 ms", "V")
m = (t > 149.5) & (t < 154)
ax[1].plot(t[m], d["v(vo5)"][m], label="5V")
ax[1].plot(t[m], d["v(v12)"][m], label="12V rail")
ax[1].plot(t[m], d["v(pg)"][m], label="PGOOD_12V")
thr(ax[1], 4.75, "CM4 min 4.75 V")
finish(ax[1], "Hold-up after U11 cuts off (zoom)", "V")
for q, lab in (("0", "earlier design"), ("1", "as built (R22/R91 divider)")):
    d = load(f"ovp_soft{q}.dat")
    t = d["time"] * 1e3
    m = (t > 140) & (t < 160)
    ax[2].plot(t[m], d["vgsq2"][m], label=lab)
thr(ax[2], -20, "Q2 VGS rating -20 V")
ax[2].set_ylim(-22, 0)
finish(ax[2], "Q2 gate-source voltage", "V")
fig.tight_layout()
fig.savefig(os.path.join(R, "ovp.png"), dpi=110)
print("wrote", R)
